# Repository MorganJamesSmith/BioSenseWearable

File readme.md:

# P21

## Building the Project

The project can be built either with the Makefile in the gcc folder in order to
use the arm-none-eabi-gcc toolchain or with the Segger Embedded Studio project
in the ses folder.

The SES project and Makefile are both configured to build the project for the
nRF52840 Dongle (PCA10059). The Makefile can also be used to build the project 
for the nRF5284-DK (PCA10056) by setting an additional variable when running
make (`make BOARD=BOARD_PCA10056`).

## Programming the Board

If using the Makefile, the board can be programmed through gdb with
`make debug`, which will start and OpenOCD instance and launch a GDB session
conneted to it. To debug the board with a Black Magic Probe, use the `GDB_FILE`
variable to specify the probe's serial port. For example,
`make debug GDB_FILE=/dev/ttyACM0`.

## Licensing

The folder nRF5_SDK_17.0.0 is third-party code subject to its own licenses.

All other intellectual property in this repository (code, hardware designs,
documentation, etc.) is provided under the BSD-3 clause license (SPDX:
BSD-3-Clause https://spdx.org/licenses/BSD-3-Clause.html).

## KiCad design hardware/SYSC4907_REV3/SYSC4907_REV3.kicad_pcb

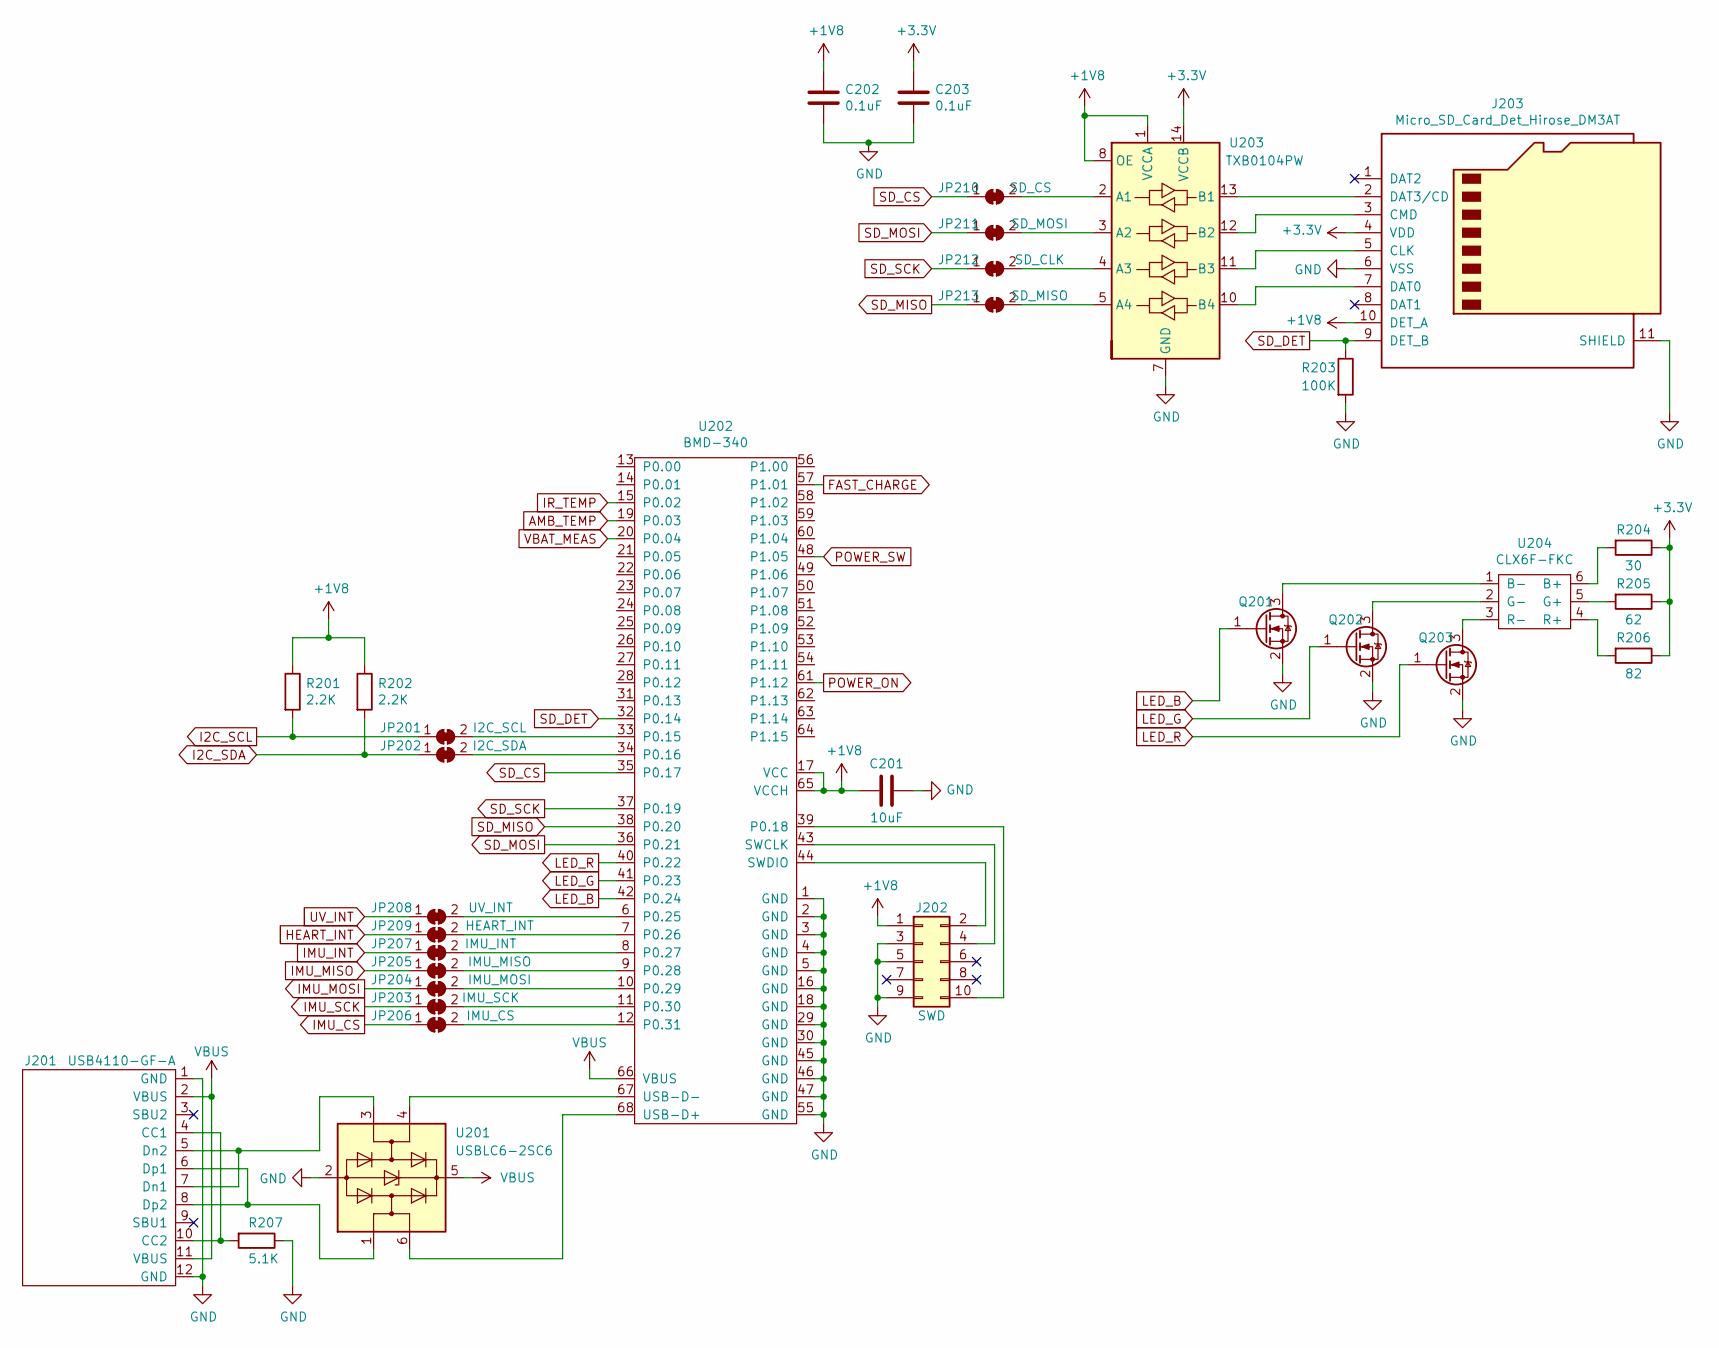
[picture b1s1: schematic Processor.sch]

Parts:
C201: 10uF; C_0603_1608Metric_Pad1.08x0.95mm_HandSolder
C202, C203: 0.1uF; C_0603_1608Metric_Pad1.08x0.95mm_HandSolder
J201: USB4110-GF-A; MPN USB4110-GF-A
J202: SWD; PinHeader_2x05_P1.27mm_Vertical_SMD; MPN FTS-105-01-L-DV
J203: Micro_SD_Card_Det_Hirose_DM3AT; microSD_HC_Hirose_DM3AT-SF-PEJM5; MPN DM3AT-SF-PEJM5
JP201: I2C_SCL; SolderJumper-2_P1.3mm_Bridged_Pad1.0x1.5mm
JP202: I2C_SDA; SolderJumper-2_P1.3mm_Bridged_Pad1.0x1.5mm
JP203: IMU_SCK; SolderJumper-2_P1.3mm_Bridged_Pad1.0x1.5mm
JP204: IMU_MOSI; SolderJumper-2_P1.3mm_Bridged_Pad1.0x1.5mm
JP205: IMU_MISO; SolderJumper-2_P1.3mm_Bridged_Pad1.0x1.5mm
JP206: IMU_CS; SolderJumper-2_P1.3mm_Bridged_Pad1.0x1.5mm
JP207: IMU_INT; SolderJumper-2_P1.3mm_Bridged_Pad1.0x1.5mm
JP208: UV_INT; SolderJumper-2_P1.3mm_Bridged_Pad1.0x1.5mm
JP209: HEART_INT; SolderJumper-2_P1.3mm_Bridged_Pad1.0x1.5mm
JP210: SD_CS; SolderJumper-2_P1.3mm_Bridged_Pad1.0x1.5mm
JP211: SD_MOSI; SolderJumper-2_P1.3mm_Bridged_Pad1.0x1.5mm
JP212: SD_CLK; SolderJumper-2_P1.3mm_Bridged_Pad1.0x1.5mm
JP213: SD_MISO; SolderJumper-2_P1.3mm_Bridged_Pad1.0x1.5mm
Q201, Q202, Q203: DMG1012T; SOT-523; MPN DMG1012T
R201, R202: 2.2K; R_0603_1608Metric_Pad0.98x0.95mm_HandSolder
R203: 100K; R_0603_1608Metric_Pad0.98x0.95mm_HandSolder
R204: 30; R_0603_1608Metric_Pad0.98x0.95mm_HandSolder
R205: 62; R_0603_1608Metric_Pad0.98x0.95mm_HandSolder
R206: 82; R_0603_1608Metric_Pad0.98x0.95mm_HandSolder
R207: 5.1K; R_0603_1608Metric_Pad0.98x0.95mm_HandSolder
U201: USBLC6-2SC6; SOT-23-6; MPN USBLC6-2SC6
U202: BMD-340; BMD-340-A-R; MPN BMD-340
U203: TXB0104PW; TSSOP-14_4.4x5mm_P0.65mm; MPN TXB0104PW
U204: CLX6F-FKC; MPN CLX6F-FKC

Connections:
+1V8: C201.2, C202.1, J202.1, J203.10 (DET_A), R201.1, R202.1, U202.17 (VCC), U202.65 (VCCH), U203.1 (VCCA), U203.8 (OE); also elsewhere on the board
+3V3: C203.1, J203.4 (VDD), R204.1, R205.1, R206.1, U203.14 (VCCB); also elsewhere on the board
AMB_TEMP: U202.19 (P0.03); also elsewhere on the board
FAST_CHARGE: U202.57 (P1.01); also elsewhere on the board
GND: C201.1, C202.2, C203.2, J201.1 (GND), J201.12 (GND), J202.3, J202.5, J202.9, J203.6 (VSS), J203.11 (SHIELD), Q201.2 (S), Q202.2 (S), Q203.2 (S), R203.2, R207.1, U201.2 (GND), U202.1 (GND), U202.2 (GND), U202.3 (GND), U202.4 (GND), U202.5 (GND), U202.16 (GND), U202.18 (GND), U202.29 (GND), U202.30 (GND), U202.45 (GND), U202.46 (GND), U202.47 (GND), U202.55 (GND), U203.7 (GND); also elsewhere on the board
HEART_INT: JP209.1 (A); also elsewhere on the board
I2C_SCL: JP201.1 (A), R201.2; also elsewhere on the board
I2C_SDA: JP202.1 (A), R202.2; also elsewhere on the board
IMU_CS: JP206.1 (A); also elsewhere on the board
IMU_INT: JP207.1 (A); also elsewhere on the board
IMU_MISO: JP205.1 (A); also elsewhere on the board
IMU_MOSI: JP204.1 (A); also elsewhere on the board
IMU_SCK: JP203.1 (A); also elsewhere on the board
IR_TEMP: U202.15 (P0.02); also elsewhere on the board
LED_B: Q201.1 (G), U202.42 (P0.24)
LED_G: Q202.1 (G), U202.41 (P0.23)
LED_R: Q203.1 (G), U202.40 (P0.22)
unnamed: J201.5 (Dn2), J201.7 (Dn1), U201.3 (I/O2)
unnamed: J201.6 (Dp1), J201.8 (Dp2), U201.1 (I/O1)
unnamed: J201.4 (CC1), J201.10 (CC2), R207.2
unnamed: J202.2, U202.44 (SWDIO)
unnamed: J202.4, U202.43 (SWCLK)
unnamed: J202.10, U202.39 (P0.18)
unnamed: J203.2 (DAT3/CD), U203.13 (B1)
unnamed: J203.3 (CMD), U203.12 (B2)
unnamed: J203.5 (CLK), U203.11 (B3)
unnamed: J203.7 (DAT0), U203.10 (B4)
unnamed: JP201.2 (B), U202.33 (P0.15)
unnamed: JP202.2 (B), U202.34 (P0.16)
unnamed: JP203.2 (B), U202.11 (P0.30)
unnamed: JP204.2 (B), U202.10 (P0.29)
unnamed: JP205.2 (B), U202.9 (P0.28)
unnamed: JP206.2 (B), U202.12 (P0.31)
unnamed: JP207.2 (B), U202.8 (P0.27)
unnamed: JP208.2 (B), U202.6 (P0.25)
unnamed: JP209.2 (B), U202.7 (P0.26)
unnamed: JP210.2 (B), U203.2 (A1)
unnamed: JP211.2 (B), U203.3 (A2)
unnamed: JP212.2 (B), U203.4 (A3)
unnamed: JP213.2 (B), U203.5 (A4)
unnamed: Q201.3 (D), U204.1 (B-)
unnamed: Q202.3 (D), U204.2 (G-)
unnamed: Q203.3 (D), U204.3 (R-)
unnamed: R204.2, U204.6 (B+)
unnamed: R205.2, U204.5 (G+)
unnamed: R206.2, U204.4 (R+)
unnamed: U201.4 (I/O2), U202.67 (USB-D-)
unnamed: U201.6 (I/O1), U202.68 (USB-D+)
POWER_ON: U202.61 (P1.12); also elsewhere on the board
POWER_SW: U202.48 (P1.05); also elsewhere on the board
SD_CS: JP210.1 (A), U202.35 (P0.17)
SD_DET: J203.9 (DET_B), R203.1, U202.32 (P0.14)
SD_MISO: JP213.1 (A), U202.38 (P0.20)
SD_MOSI: JP211.1 (A), U202.36 (P0.21)
SD_SCK: JP212.1 (A), U202.37 (P0.19)
UV_INT: JP208.1 (A); also elsewhere on the board
VBAT_MEAS: U202.20 (P0.04); also elsewhere on the board
VBUS: J201.2 (VBUS), J201.11 (VBUS), U201.5 (VBUS), U202.66 (VBUS); also elsewhere on the board

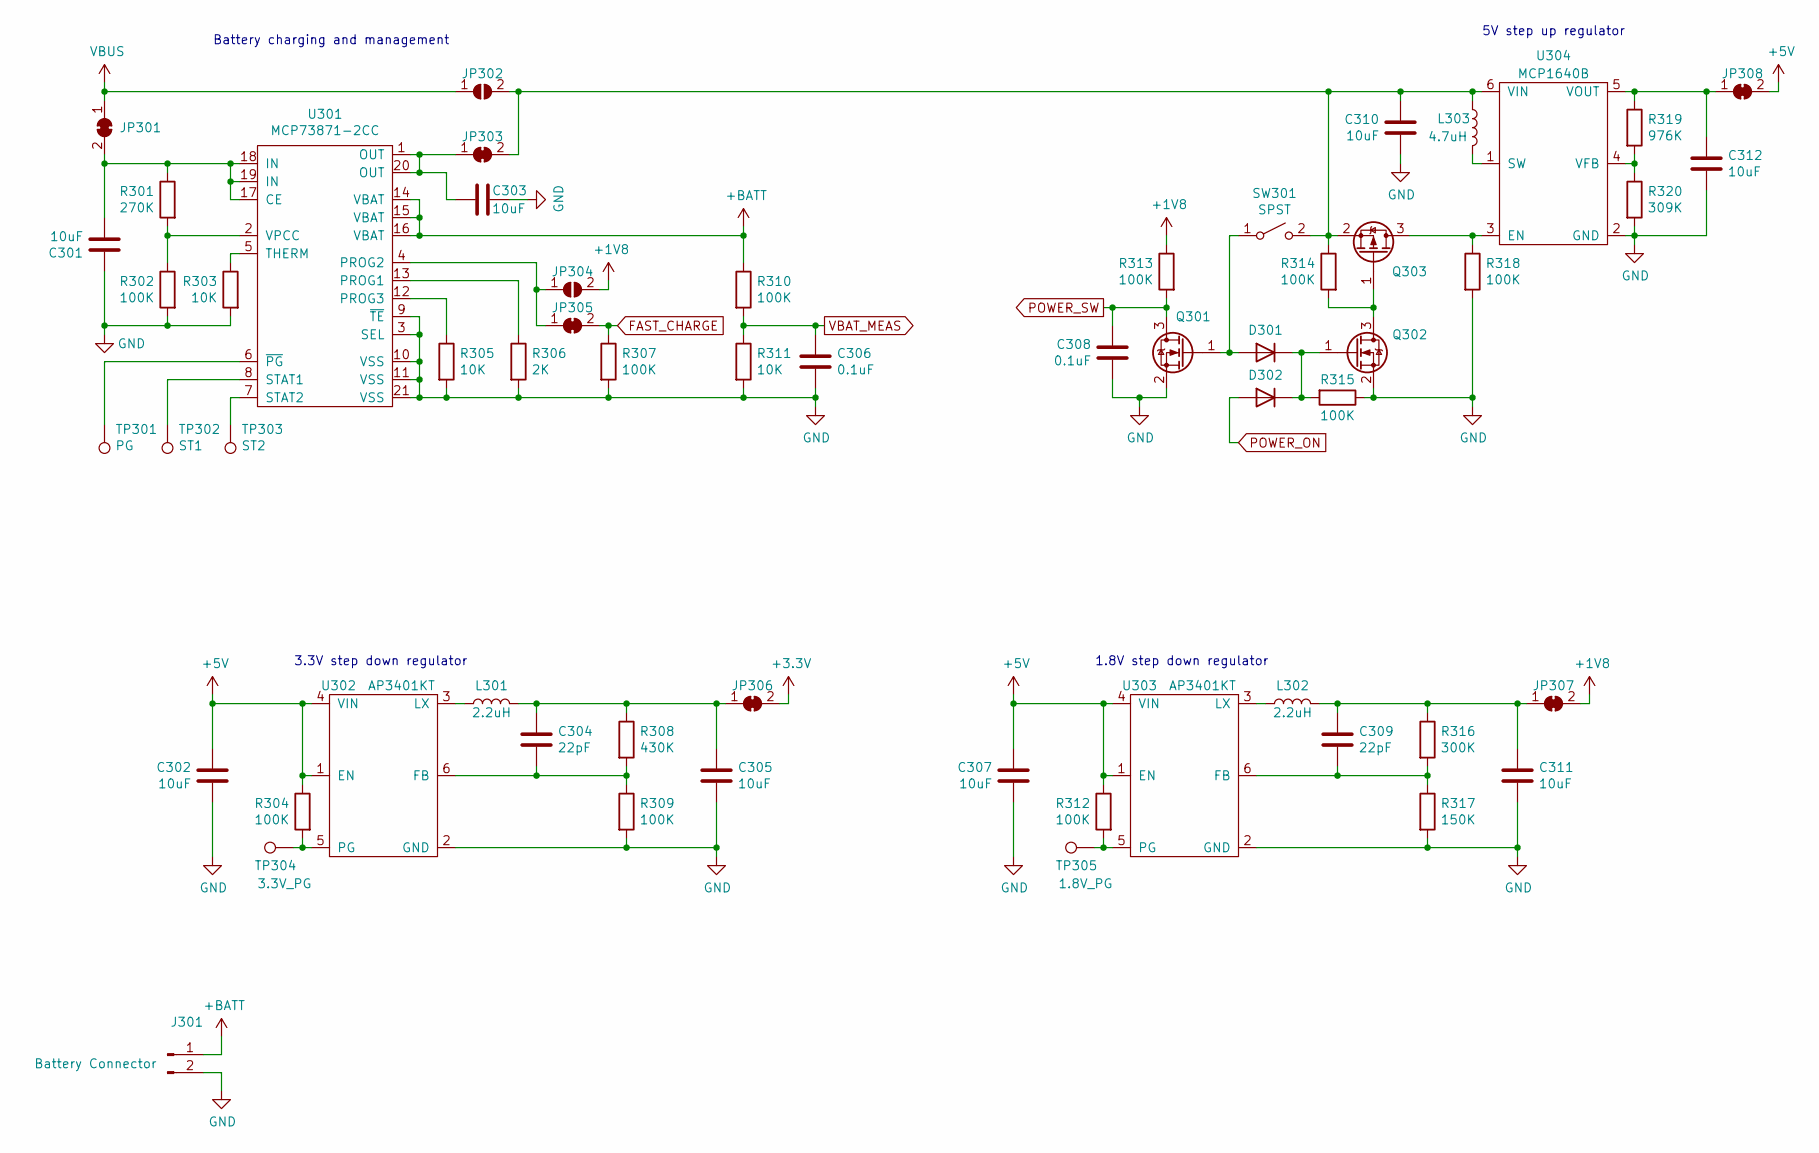
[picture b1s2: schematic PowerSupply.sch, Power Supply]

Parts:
C301, C302, C303, C305, C307, C310, C311, C312: 10uF; C_0603_1608Metric_Pad1.08x0.95mm_HandSolder
C304, C309: 22pF; C_0603_1608Metric_Pad1.08x0.95mm_HandSolder
C306, C308: 0.1uF; C_0603_1608Metric_Pad1.08x0.95mm_HandSolder
D301, D302: NSR0530HT1G; D_SOD-323_HandSoldering; MPN NSR0530HT1G
J301: Battery Connector; PinHeader_1x02_P2.54mm_Vertical
JP301, JP303, JP305, JP306, JP307, JP308: Bridged; SolderJumper-2_P1.3mm_Bridged_Pad1.0x1.5mm
JP302, JP304: Open; SolderJumper-2_P1.3mm_Open_Pad1.0x1.5mm
L301, L302: 2.2uH; L_Taiyo-Yuden_NR-30xx_HandSoldering; MPN NRH3012T2R2MN
L303: 4.7uH; L_Taiyo-Yuden_NR-30xx_HandSoldering; MPN NRH3012T4R7MN
Q301, Q302: DMG1012T; SOT-523; MPN DMG1012T
Q303: DMG1013T; SOT-523; MPN DMG1013T
R301: 270K; R_0603_1608Metric_Pad0.98x0.95mm_HandSolder
R302, R304, R307, R309, R310, R312, R313, R314, R315, R318: 100K; R_0603_1608Metric_Pad0.98x0.95mm_HandSolder
R303, R305, R311: 10K; R_0603_1608Metric_Pad0.98x0.95mm_HandSolder
R306: 2K; R_0603_1608Metric_Pad0.98x0.95mm_HandSolder
R308: 430K; R_0603_1608Metric_Pad0.98x0.95mm_HandSolder
R316: 300K; R_0603_1608Metric_Pad0.98x0.95mm_HandSolder
R317: 150K; R_0603_1608Metric_Pad0.98x0.95mm_HandSolder
R319: 976K; R_0603_1608Metric_Pad0.98x0.95mm_HandSolder
R320: 309K; R_0603_1608Metric_Pad0.98x0.95mm_HandSolder
SW301: SPST; EVQ-P7C01P; MPN EVQ-P7C01P
TP301: PG; TestPoint_Pad_D1.0mm
TP302: ST1; TestPoint_Pad_D1.0mm
TP303: ST2; TestPoint_Pad_D1.0mm
TP304: 3.3V_PG; TestPoint_Pad_D1.0mm
TP305: 1.8V_PG; TestPoint_Pad_D1.0mm
U301: MCP73871-2CC; QFN-20-1EP_4x4mm_P0.5mm_EP2.7x2.7mm; MPN MCP73871-2CC
U302, U303: AP3401KT; TSOT-23-6; MPN AP3401KT
U304: MCP1640B; SOT-23-6; MPN MCP1640B

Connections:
+1V8: JP304.2 (B), JP307.2 (B), R313.1; also elsewhere on the board
+3V3: JP306.2 (B); also elsewhere on the board
+5V: C302.1, C307.1, JP308.2 (B), R304.1, R312.1, U302.1 (EN), U302.4 (VIN), U303.1 (EN), U303.4 (VIN)
+BATT: J301.1, R310.1, U301.14 (VBAT), U301.15 (VBAT), U301.16 (VBAT)
FAST_CHARGE: JP305.2 (B), R307.1; also elsewhere on the board
GND: C301.1, C302.2, C303.1, C305.2, C306.2, C307.2, C308.2, C310.2, C311.2, C312.2, J301.2, Q301.2 (S), Q302.2 (S), R302.2, R303.2, R305.2, R306.2, R307.2, R309.2, R311.2, R315.1, R317.2, R318.2, R320.2, U301.3 (SEL), U301.9 (~TE), U301.10 (VSS), U301.11 (VSS), U301.21 (VSS), U302.2 (GND), U303.2 (GND), U304.2 (GND); also elsewhere on the board
unnamed: C301.2, JP301.2 (B), R301.1, U301.17 (CE), U301.18 (IN), U301.19 (IN)
unnamed: C303.2, JP303.1 (A), U301.1 (OUT), U301.20 (OUT)
unnamed: C304.1, C305.1, JP306.1 (A), L301.1, R308.1
unnamed: C304.2, R308.2, R309.1, U302.6 (FB)
unnamed: C309.1, C311.1, JP307.1 (A), L302.1, R316.1
unnamed: C309.2, R316.2, R317.1, U303.6 (FB)
unnamed: C310.1, JP302.2 (B), JP303.2 (B), L303.1, Q303.2 (S), R314.1, SW301.2 (B), U304.6 (VIN)
unnamed: C312.1, JP308.1 (A), R319.1, U304.5 (VOUT)
unnamed: D301.1 (K), D302.1 (K), Q302.1 (G), R315.2
unnamed: D301.2 (A), Q301.1 (G), SW301.1 (A)
unnamed: JP304.1 (A), JP305.1 (A), U301.4 (PROG2)
unnamed: L301.2, U302.3 (LX)
unnamed: L302.2, U303.3 (LX)
unnamed: L303.2, U304.1 (SW)
unnamed: Q302.3 (D), Q303.1 (G), R314.2
unnamed: Q303.3 (D), R318.1, U304.3 (EN)
unnamed: R301.2, R302.1, U301.2 (VPCC)
unnamed: R303.1, U301.5 (THERM)
unnamed: R304.2, TP304.1, U302.5 (PG)
unnamed: R305.1, U301.12 (PROG3)
unnamed: R306.1, U301.13 (PROG1)
unnamed: R312.2, TP305.1, U303.5 (PG)
unnamed: R319.2, R320.1, U304.4 (VFB)
unnamed: TP301.1, U301.6 (~PG)
unnamed: TP302.1, U301.8 (STAT1)
unnamed: TP303.1, U301.7 (STAT2)
POWER_ON: D302.2 (A); also elsewhere on the board
POWER_SW: C308.1, Q301.3 (D), R313.2; also elsewhere on the board
VBAT_MEAS: C306.1, R310.2, R311.1; also elsewhere on the board
VBUS: JP301.1 (A), JP302.1 (A); also elsewhere on the board

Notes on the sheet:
3.3V step down regulator
1.8V step down regulator
5V step up regulator
Battery charging and management

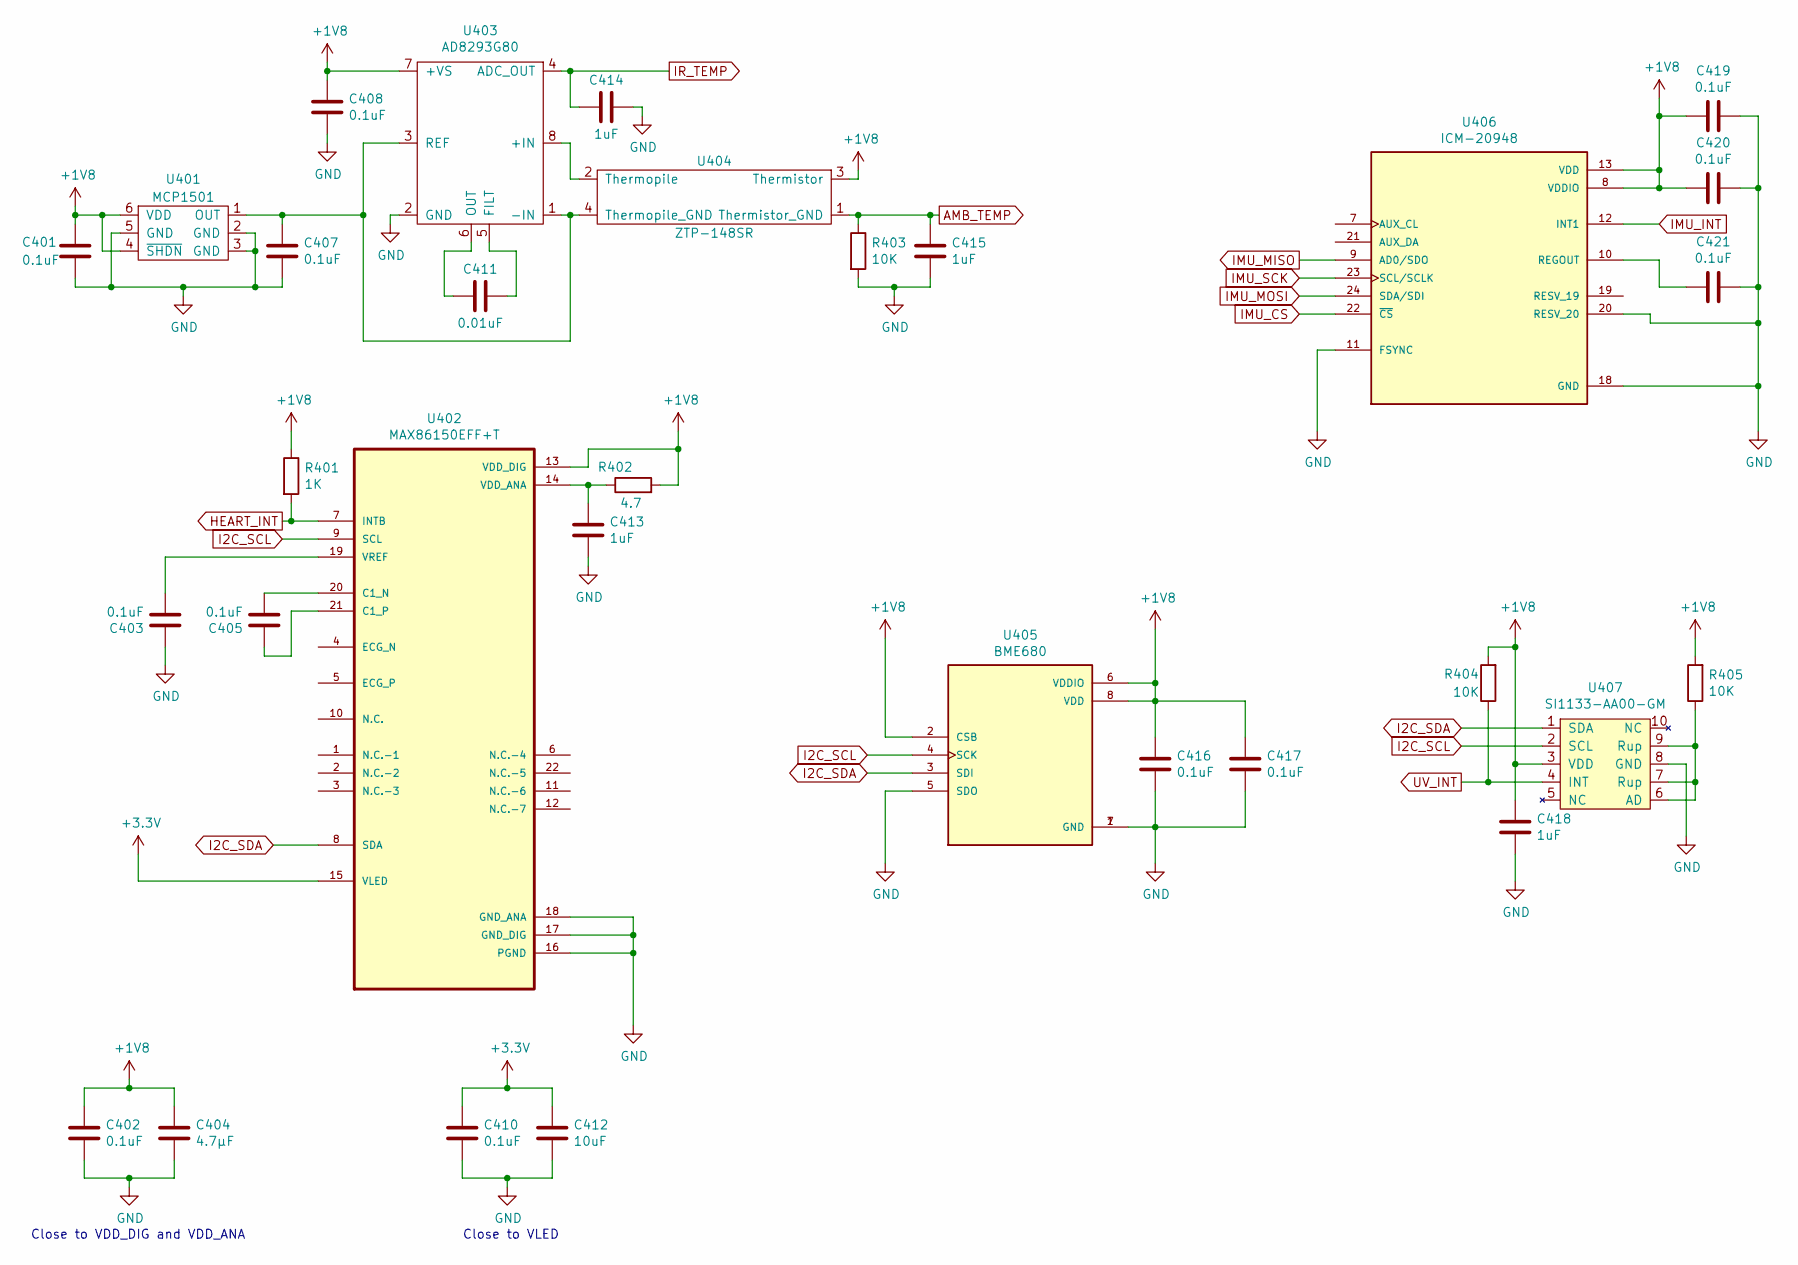
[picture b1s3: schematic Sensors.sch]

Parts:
C401, C402, C403, C405, C407, C408, C410, C416, C417, C419, C420, C421: 0.1uF; C_0603_1608Metric_Pad1.08x0.95mm_HandSolder
C404: 4.7µF; C_0603_1608Metric_Pad1.08x0.95mm_HandSolder
C411: 0.01uF; C_0603_1608Metric_Pad1.08x0.95mm_HandSolder
C412: 10uF; C_0603_1608Metric_Pad1.08x0.95mm_HandSolder
C413, C414, C415, C418: 1uF; C_0603_1608Metric_Pad1.08x0.95mm_HandSolder
R401: 1K; R_0603_1608Metric_Pad0.98x0.95mm_HandSolder
R402: 4.7; R_0603_1608Metric_Pad0.98x0.95mm_HandSolder
R403, R404, R405: 10K; R_0603_1608Metric_Pad0.98x0.95mm_HandSolder
U401: MCP1501; SOT-23-6; MPN MCP1501T-10E/CHY
U402: MAX86150EFF+T; MPN MAX86150EFF+T
U403: AD8293G80; SOT-23-8; MPN AD8293G80
U404: ZTP-148SR; MPN ZTP-148SR
U405: BME680; Bosch_LGA-8_3x3mm_P0.8mm_ClockwisePinNumbering; MPN BME680
U406: ICM-20948; QFN-24-1EP_3x3mm_P0.4mm_EP1.75x1.6mm; MPN ICM-20948
U407: SI1133-AA00-GM; MPN SI1133-AA00-GM

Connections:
+1V8: C401.1, C402.1, C404.1, C408.1, C416.1, C417.1, C418.2, C419.2, C420.2, R401.1, R402.2, R404.2, R405.2, U401.4 (~SHDN), U401.6 (VDD), U402.13 (VDD_DIG), U403.7 (+VS), U404.3 (Thermistor), U405.2 (CSB), U405.6 (VDDIO), U405.8 (VDD), U406.8 (VDDIO), U406.13 (VDD), U407.3 (VDD); also elsewhere on the board
+3V3: C410.1, C412.1, U402.15 (VLED); also elsewhere on the board
AMB_TEMP: C415.1, R403.1, U404.1 (Thermistor_GND); also elsewhere on the board
GND: C401.2, C402.2, C403.1, C404.2, C407.2, C408.2, C410.2, C412.2, C413.2, C414.1, C415.2, C416.2, C417.2, C418.1, C419.1, C420.1, C421.1, R403.2, U401.2 (GND), U401.3 (GND), U401.5 (GND), U402.16 (PGND), U402.17 (GND_DIG), U402.18 (GND_ANA), U403.2 (GND), U405.1 (GND), U405.5 (SDO), U405.7 (GND), U406.11 (FSYNC), U406.18 (GND), U406.20 (RESV_20), U407.8 (GND); also elsewhere on the board
HEART_INT: R401.2, U402.7 (INTB); also elsewhere on the board
I2C_SCL: U402.9 (SCL), U405.4 (SCK), U407.2 (SCL); also elsewhere on the board
I2C_SDA: U402.8 (SDA), U405.3 (SDI), U407.1 (SDA); also elsewhere on the board
IMU_CS: U406.22 (~CS); also elsewhere on the board
IMU_INT: U406.12 (INT1); also elsewhere on the board
IMU_MISO: U406.9 (AD0/SDO); also elsewhere on the board
IMU_MOSI: U406.24 (SDA/SDI); also elsewhere on the board
IMU_SCK: U406.23 (SCL/SCLK); also elsewhere on the board
IR_TEMP: C414.2, U403.4 (ADC_OUT); also elsewhere on the board
unnamed: C403.2, U402.19 (VREF)
unnamed: C405.1, U402.21 (C1_P)
unnamed: C405.2, U402.20 (C1_N)
unnamed: C407.1, U401.1 (OUT), U403.1 (-IN), U403.3 (REF), U404.4 (Thermopile_GND)
unnamed: C411.1, U403.5 (FILT)
unnamed: C411.2, U403.6 (OUT)
unnamed: C413.1, R402.1, U402.14 (VDD_ANA)
unnamed: C421.2, U406.10 (REGOUT)
unnamed: R405.1, U407.6 (AD), U407.7 (Rup), U407.9 (Rup)
unnamed: U403.8 (+IN), U404.2 (Thermopile)
UV_INT: R404.1, U407.4 (INT); also elsewhere on the board

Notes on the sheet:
Close to VDD_DIG and VDD_ANA
Close to VLED

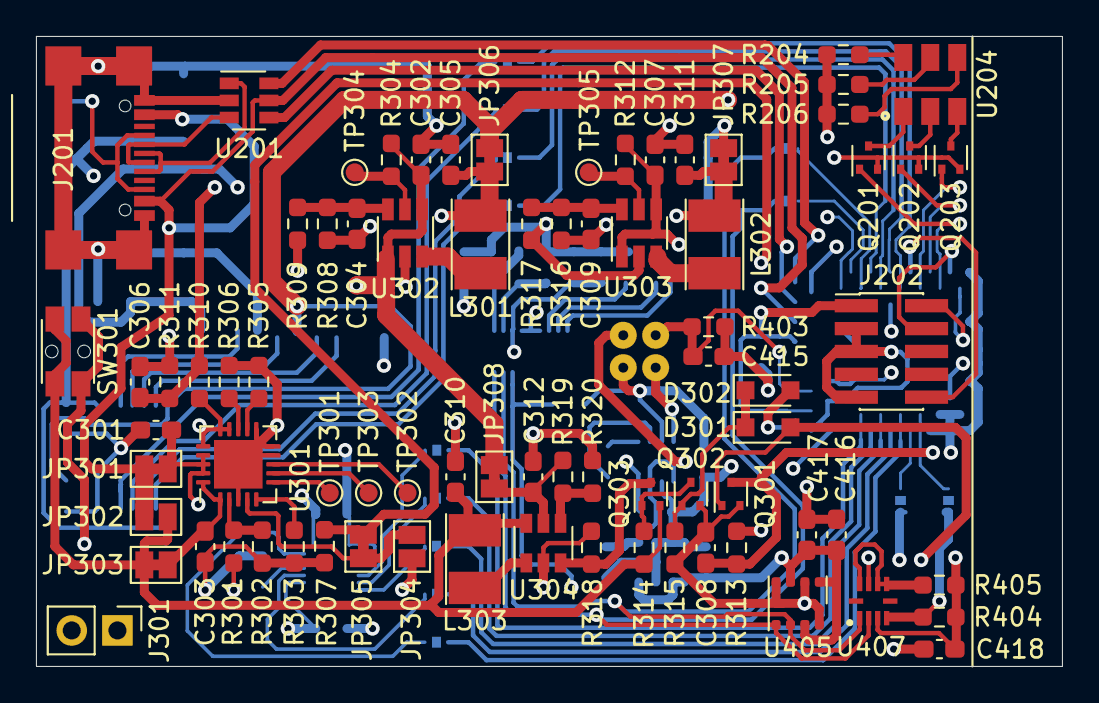
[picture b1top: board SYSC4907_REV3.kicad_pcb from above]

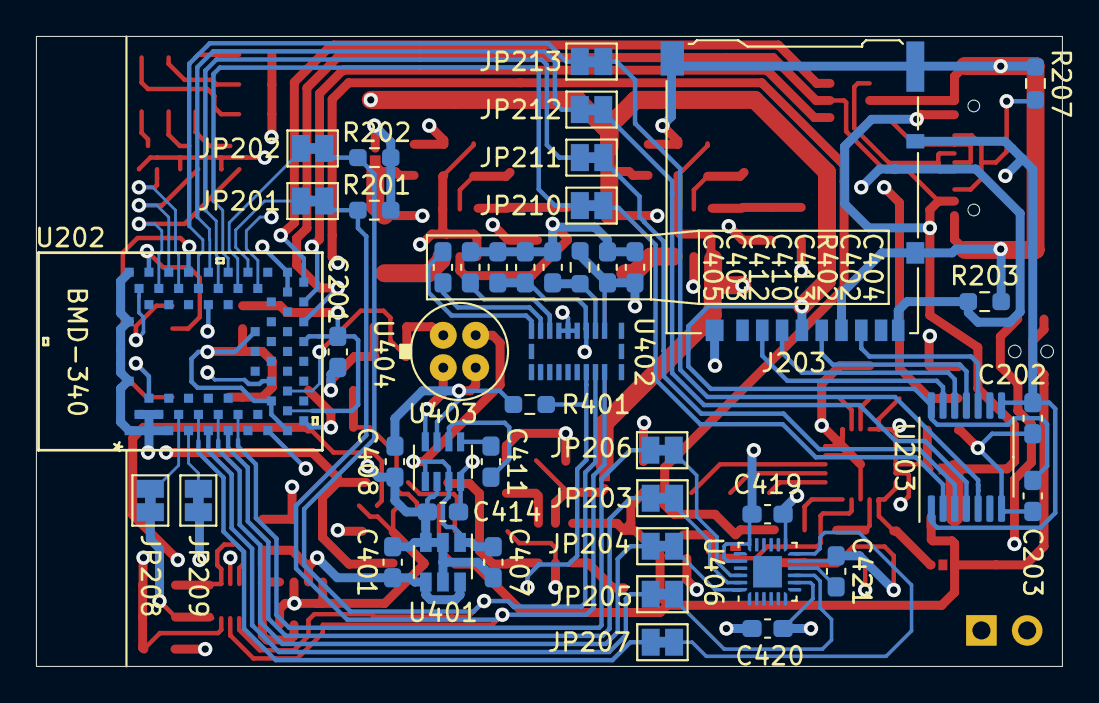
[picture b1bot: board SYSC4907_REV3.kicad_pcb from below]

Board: 4 copper layers, 57.0 x 35.0 mm, 123 parts (45 on the bottom side), 96 nets.

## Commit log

2020-05-12 init commit
2020-05-12 Renamed ideas.org to readme.org
2020-05-15 Add some new possible features and a new idea
2020-05-16 Added first imaginings
2020-06-10 Updated with our confirmed project idea + added more info
2020-06-10 formatting
2020-09-21 Update readme with more research
2020-09-26 Update sensors list
2020-12-24 Add project skeleton
2021-01-16 Add initial enclosure model
2021-01-21 consolidated variables, added main_board, adjusted values
2021-02-02 Implement debugging command line over USB CDC ACM interface
2021-02-04 add guix build file
2021-02-07 Added Bluetooth serial interface
2021-02-17 add Bluetooth terminal emulator to access Bluetooth CLI
2021-02-17 Add module to read analog inputs
2021-02-17 Remove unused variable in bluetooth.c
2021-02-18 Add IMU driver
2021-02-18 fixed TX overflow, tested Bluetooth connection callbacks with PC app
2021-02-19 use short commit for guix build
2021-02-19 add max86150 research
2021-02-19 fixed USB & Bluetooth compatibility problem
2021-02-19 Add external max86150 library
    These will have to heavily modified since they aren't even in the right
    language
2021-02-19 update max86150 headers to indicate changes will be made
2021-02-19 max86150: line up constants
2021-02-19 max86150: change many Arduino things into their c counterpart
    Also replaced tabs with spaces
2021-02-19 max86150: fix whitespace
2021-02-21 Copy proposal to create final report template
2021-02-21 add partial work for UV light sensor
2021-02-21 Update structure of final report
2021-02-22 Fix title page of final report
2021-02-22 added chapter 1 & 2 content and state of the art
2021-02-22 added board designs to repo and made corrections to REV2 schematic and layout
2021-02-22 added updated schematics and board design to appendices, and updated overview
2021-02-22 added and tweaked existing challenges from progress report
2021-02-23 finished copying sections from progress report and changing tense
2021-02-23 finished hardware section
2021-02-24 added Bluetooth to software implementation
2021-02-24 started adding project contributions
2021-02-24 added Bluetooth software challenge
2021-02-25 added my reflection
2021-02-26 final report: Fix spelling
2021-02-26 final report: update COVID-19 death toll
2021-02-27 final report: copy enclosure section from proposal verbatim
2021-02-27 enclosure: make nub position dependent on nub size
2021-02-27 enclosure: make global variables for component size and location
2021-02-27 enclosure: add top_thickness variable
2021-02-27 enclosure: add cutouts for sensors, USB, and SD card
2021-02-27 final report: Add enclosure render
2021-02-27 final report (enclosure): change tense to past tense
2021-02-28 final report: Add reflection
2021-02-28 final report: add assembly and parts availability challenges
2021-02-28 final report: enable bibliography
2021-02-28 final report: Add heart rate driver section
2021-02-28 final report (enclosure appendix): Fix formatting
2021-02-28 final report: add timeline section
2021-02-28 add Part 2 for engineering
2021-02-28 update engineering section to use full sentences,
2021-02-28 final report: split software challenges in to subsubsections
2021-02-28 final report: update contributions
2021-03-01 final report: replace where with were where appropriate
2021-03-01 final report: update firmware block diagram
2021-03-01 final report: add subsubsetions for USB and IMU drivers
2021-03-01 final report: add photos of board
2021-03-01 final report: add lists of figures and tables
2021-03-01 reflection added
2021-03-01 final report: Add accomplishments section
2021-03-01 final report: Add abstract section
2021-03-01 final report (enclosure): change me to us
2021-03-01 final report: Add testing section
2021-03-01 kira review
2021-03-01 final report: adjust size of board photos to avoid mostly blank page
2021-03-02 added first draft of companion app parser.py will input a log file and spit out several csv files for each type of data. Further work will be needed for bluetooth and other stuff but assuming we have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
2021-03-04 Implement data logging
2021-03-04 updated companion, confirmed it works with log file
2021-03-04 initial bluetooth based on Jason's code mostly copied Jasons code but made it a async generator
2021-03-08 fix zero thickness geometries in enclosure
2021-03-08 add script to generate enclosure renders
2021-03-08 Comment out some stuff in gitignore to allow protothreads library to be commited
2021-03-11 license project using BSD-3-Clause license
2021-03-14 Configure interrupt priorities
2021-03-14 Add ability to provide offset and/or length as parameters to hcat command
2021-03-14 Add time command for logging current unix time
2021-03-14 Add buffering to data logger
2021-03-14 added time alignment struct also updated bluetooth code to scan indefinitely
2021-03-14 added temp and voltage log structs
2021-03-14 Fix issue where reset data entries where not properly logged
2021-03-14 pedantic comments spacing
2021-03-14 ignore pycache, added companion app readme
2021-03-14 plotting code
2021-03-14 do not require entries to be strictly increasing timestamps
2021-03-14 Fix setting of adc_samples_pending flag in adc.c
2021-03-15 units for demo also units comments clarifications
2021-03-15 added usb communication
2021-03-15 added first test for live data stuff
2021-03-15 update live logging code
2021-03-16 test for live plotting
2021-03-16 Enclosure changes
    refactored code
    added x_overextrusion variable
    added more cutouts
2021-03-19 update enclosure
2021-03-20 enclosure updates
2021-03-26 updated state of the art
2021-03-26 updated final report hardware implementation
2021-03-27 updated final report problem statement
2021-03-29 test cases for companion app
2021-03-29 test plan stuff in readme
2021-04-10 Fix names of ICM20948 pin constants to say SPI instead of I2C
2021-04-12 Consolidate configuration options in header
2021-04-12 Add profiling code for making time measurments
2021-04-12 Add discussion of timing results to final report
2021-04-12 Fix spelling and grammar errors in testing section of final report
2021-04-12 Rename sections in final report as suggested by Prof. Garcia
2021-04-12 Fix time values in final report testing section that where corrupted by floating point error
2021-04-12 Rearrange sections
    Abstract is now after the title page
    Enclosure is now part of hardware
2021-04-12 Rearange software section of final report
2021-04-12 added companion app testing also credit for companion app
2021-04-12 corrected companion app testing header for sam's work
2021-04-12 Fix build error when profiling is disabled
2021-04-12 Disable compilation of SD card related CLI commands when SD card is disabled
2021-04-12 Fix compilation errors when bluetooth is disabled
2021-04-12 Fix errors when compiling with IMU disabled
2021-04-13 first run of companion software description needs revision tomorrow
2021-04-13 shh don't worry about it
2021-04-13 Update software section of final report
2021-04-13 Add integration testing content and board weight to final report testing section
2021-04-13 final report: Add all gantt charts
2021-04-13 final report: Fix overlap in legend
2021-04-13 update intro and conclusion
2021-04-13 temp
2021-04-13 companion app figure and engineering section rewording
2021-04-13 added missing image
2021-04-14 added electrical specifications
2021-04-14 final report: Update enclosure section
2021-04-14 final enclosure changes
2021-04-14 final report: Update physical dimensions section
2021-04-14 final report: Update timeline and timeline-appendix sections
2021-04-14 final report: Update abstract section
2021-04-14 updated info about sensors completed in all three places
2021-04-14 address first feedback on accomplishment specificity
2021-04-14 final report: Enable gnuplot figure generation
2021-04-14 macro for cost of board
2021-04-14 fix companion app flow chart size
2021-04-14 attempt at improving beginning of intro
2021-04-14 bib changes
2021-04-14 final report: Make appendices nicer
2021-04-14 final report: minor tweaks
2021-04-14 abstract and intro for sensor descriptions also future tence for solutions section, still uses "will" in a case which is not specifically future tense, think it is fine.
    also plot file for video
2021-04-14 final report: Update weight
2021-04-14 add more background to intro
2021-04-14 Update software challenges section in final report
2021-04-14 Add cost information and BOM to final report
2021-04-14 Fix tense in software section of final report
2021-04-14 conclusion
2021-04-14 Update formating of components list in final report
2021-04-14 Update board cost in final report
2021-04-14 small fixes
2021-04-14 abstract tweak
2021-04-14 mention SD card
2021-04-14 final report: Fix reference to list of compoenents from testing section
2021-04-14 add intro to contributions

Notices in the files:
parts and their libraries:
Copyright 2016 Accelerated Designs. All rights reserved.
